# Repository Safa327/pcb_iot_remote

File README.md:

View this project on [CADLAB.io](https://cadlab.io/project/29201). 

# pcb_iot_remote

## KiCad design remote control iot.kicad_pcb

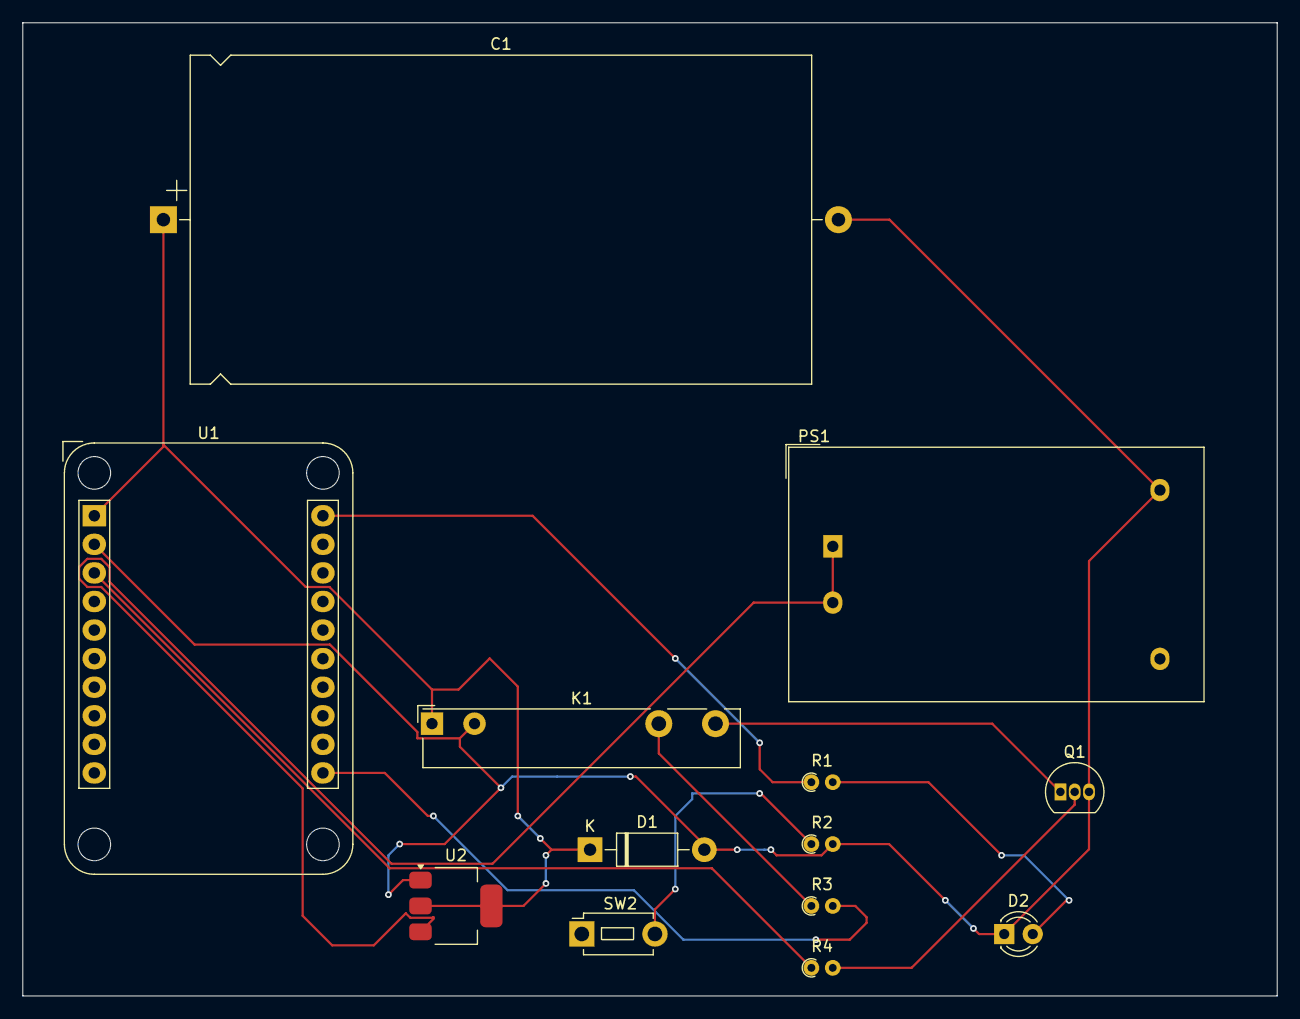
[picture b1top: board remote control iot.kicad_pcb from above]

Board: 2 copper layers, 111.5 x 86.5 mm, 13 parts (0 on the bottom side), 11 nets.

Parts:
C1: C; CP_Axial_L55.0mm_D29.0mm_P60.00mm_Horizontal
D1: 1N4007; D_DO-41_SOD81_P10.16mm_Horizontal
D2: LED; LED_D3.0mm
K1: Fujitsu_FTR-LYAA005x; Relay_SPST-NO_Fujitsu_FTR-LYAA005x_FormA_Vertical
PS1: HLK-PM01; Converter_ACDC_Hi-Link_HLK-PMxx
Q1: BC547; TO-92_Inline
R1, R2, R3, R4: R; R_Axial_DIN0204_L3.6mm_D1.6mm_P1.90mm_Vertical
SW2: SW_Push; SW_PUSH_1P1T_6x3.5mm_H4.3_APEM_MJTP1243
U1: Olimex_MOD-WIFI-ESP8266-DEV; Adafruit_HUZZAH_ESP8266_breakout_WithMountingHoles
U2: AMS1117-3.3; SOT-223-3_TabPin2

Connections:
AC: PS1.1 (AC/L), PS1.2 (AC/N), U2.3 (VI)
GND: C1.2, D1.2 (A), D2.1 (K), K1.A2, PS1.3 (-Vout), Q1.3 (E), R2.2, U1.2 (GND), U2.1 (GND)
unnamed: D2.2 (A), R1.2
unnamed: K1.13, R3.1
unnamed: Q1.2 (B), R4.2
unnamed: K1.14, Q1.1 (C)
unnamed: R2.1, SW2.2
unnamed: R4.1, U1.3 (GPIO1)
unnamed: R3.2, U1.11 (GPIO5)
unnamed: R1.1, U1.20 (GPIO-2)
VCC: C1.1, D1.1 (K), K1.A1, U1.1 (3.3V), U2.2 (VO)

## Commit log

2025-04-08 Backlink to CADLAB.io has been added.
